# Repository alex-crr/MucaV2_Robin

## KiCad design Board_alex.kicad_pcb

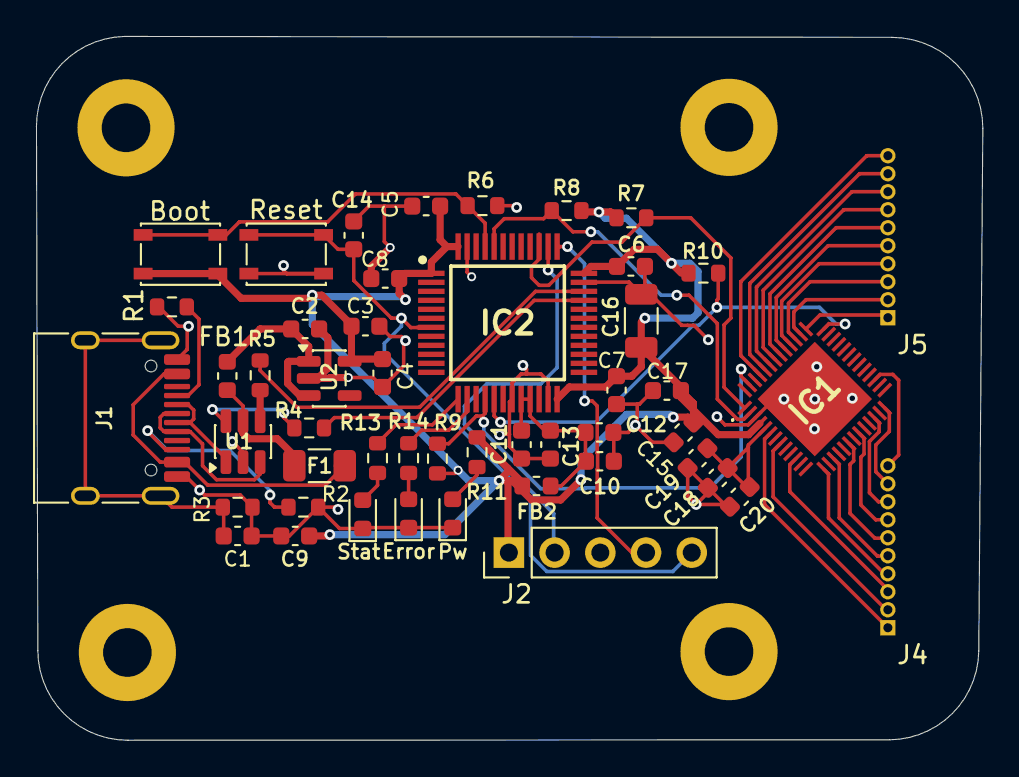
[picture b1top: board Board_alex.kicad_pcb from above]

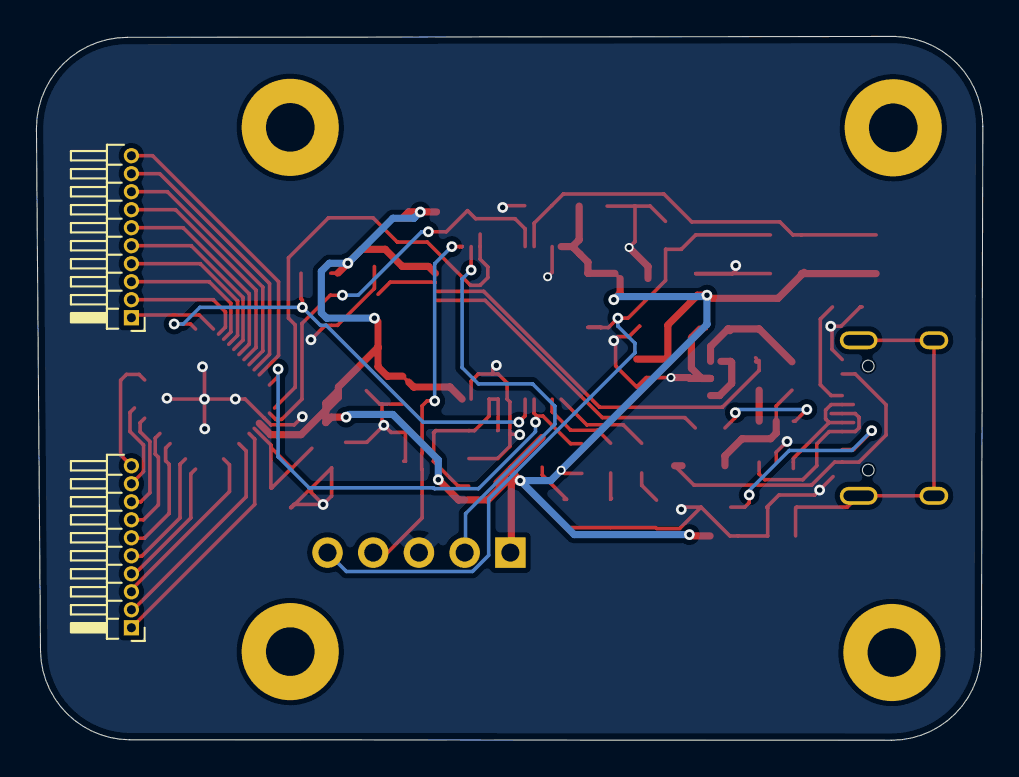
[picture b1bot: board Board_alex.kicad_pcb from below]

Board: 2 copper layers, 52.6 x 39.1 mm, 49 parts (2 on the bottom side), 49 nets.

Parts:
Boot: SW_Push; SW_SPST_PTS810
C1: C 4.7nF; C_0603_1608Metric
C2, C4: C 10uF; C_0603_1608Metric
C3, C11, C12, C20: C 1uF; C_0603_1608Metric
C5, C6, C7, C8, C10, C13, C14, C15, C19: C 100nF; C_0603_1608Metric
C9: C 4.7uF; C_0603_1608Metric
C16: C 47uF; C_1206_3216Metric
C17, C18: C 100pF; C_0603_1608Metric
Error: LED; LED_0603_1608Metric
F1: Polyfuse; Fuse_1206_3216Metric
FB1, FB2: FerriteBead; L_0603_1608Metric
IC1: IQS9150-000QFR; IQS9150000QFR
IC2: STM32G431CBT6; QFP50P900X900X160-48N
J1: USB_C_Receptacle_USB2.0_16P; USB_C_Receptacle_HRO_TYPE-C-31-M-12
J2: Conn_01x05_Pin; PinHeader_1x05_P2.54mm_Vertical
J4, J5: Conn_01x10_Pin; PinHeader_1x10_P1.00mm_Horizontal
Pw: LED; LED_0603_1608Metric
R1, R2: R 5.1k; R_0603_1608Metric
R3: R 1M; R_0603_1608Metric
R4, R5: R 22; R_0603_1608Metric
R6, R10: R 10k; R_0603_1608Metric
R7, R8, R9: R 4.7k; R_0603_1608Metric
R11, R13, R14: R 1k; R_0603_1608Metric
Reset: SW_Push; SW_SPST_PTS810
Stat: LED; LED_0603_1608Metric
U1: USBLC6-2SC6; SOT-23-6
U2: AP2112K-3.3; SOT-23-5

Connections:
+3.3V: Boot.2, C3.1, C4.1, C5.2, C6.2, C7.2, C8.2, C9.2, C15.2, C16.2, C17.2, FB2.1, IC1.4 (VDD), IC2.1 (VBAT), IC2.24 (VDD_1), IC2.36 (VDD_2), IC2.48 (VDD_3), J2.1, R7.2, R8.2, R9.1, R10.1, R11.2, U2.5 (VOUT)
+5V: C2.1, FB1.2, U2.1 (VIN), U2.3 (EN)
/Boot: Boot.1, IC2.45 (PB8-BOOT0), R6.2
/I2C_SCL: IC1.1 (SCL), IC2.39 (PA15), R7.1
/I2C_SDA: IC1.2 (SDA), IC2.44 (PB7), R8.1
/IQS_RDY: IC1.51 (RDY), IC2.16 (PB0), R9.2
/IQS_RST: IC1.39 (MCLR_/_VPP), IC2.17 (PB1), R10.2
/NRST: C14.2, IC2.7 (PG10_-_NRST), J2.5, Reset.2
/RX0: IC1.6 (RX0_/_TX0), J4.1
/RX1: IC1.8 (RX1_/_TX1), J4.2
/RX2: IC1.11 (_RX2_/_TX2), J4.3
/RX3: IC1.14 (RX3_/_TX3), J4.4
/RX4: IC1.16 (RX4_/_TX4), J4.5
/RX5: IC1.19 (RX5_/_TX5), J4.6
/RX6: IC1.21 (RX6_/_TX6), J4.7
/RX7: IC1.24 (RX7_/_TX7), J4.8
/RX8: IC1.26 (_RX8_/_TX8), J4.9
/RX9: IC1.29 (RX9_/_TX9), J4.10
/TX0: IC1.40 (TX33), J5.1
/TX1: IC1.41 (TX34), J5.2
/TX2: IC1.42 (TX35), J5.3
/TX3: IC1.43 (TX36), J5.4
/TX4: IC1.44 (TX37), J5.5
/TX5: IC1.45 (TX38), J5.6
/TX6: IC1.46 (TX39), J5.7
/TX7: IC1.47 (TX40), J5.8
/TX8: IC1.48 (TX41), J5.9
/TX9: IC1.49 (TX42), J5.10
/USB_CONN_D+: J1.A6 (D+), J1.B6 (D+), U1.3 (I/O2)
/USB_CONN_D-: J1.A7 (D-), J1.B7 (D-), U1.1 (I/O1)
/USB_D+: IC2.34 (PA12), R5.1
/USB_D-: IC2.33 (PA11), R4.2
/VBUS_PROT: F1.2, FB1.1, U1.5 (VBUS)
GND: C1.2, C2.2, C3.2, C4.2, C5.1, C6.1, C7.1, C8.1, C9.1, C10.2, C11.2, C12.2, C13.2, C14.1, C15.1, C16.1, C17.1, C18.1, C19.1, C20.1, Error.1 (K), IC1.3 (VSS), IC1.53 (GND), IC2.19 (VSSA), IC2.23 (VSS_1), IC2.35 (VSS_2), IC2.47 (VSS_3), J1.A1 (GND), J1.A12 (GND), J1.B1 (GND), J1.B12 (GND), J2.3, Pw.1 (K), R1.2, R2.2, R3.1, R6.1, Reset.1, Stat.1 (K), U1.2 (GND), U2.2 (GND)
unnamed: Error.2 (A), R14.1
unnamed: Pw.2 (A), R11.1
unnamed: R13.1, Stat.2 (A)
unnamed: F1.1, J1.A4 (VBUS), J1.A9 (VBUS), J1.B4 (VBUS), J1.B9 (VBUS)
unnamed: C18.2, C19.2, C20.2, IC1.5 (VREG)
unnamed: IC2.13 (PA5), R13.2
unnamed: IC2.14 (PA6), R14.2
unnamed: IC2.37 (PA13), J2.4
unnamed: IC2.38 (PA14), J2.2
unnamed: C10.1, C11.1, C12.1, C13.1, FB2.2, IC2.20 (VREF+), IC2.21 (VDDA)
unnamed: J1.A5 (CC1), R1.1
unnamed: J1.B5 (CC2), R2.1
unnamed: C1.1, J1.SH (SHIELD), R3.2
unnamed: R4.1, U1.6 (I/O1)
unnamed: R5.2, U1.4 (I/O2)

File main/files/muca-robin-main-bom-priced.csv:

Designators,Value,Footprint,Qty/Board,LCSC Part #,JLC Type,JLC Stock,LCSC Stock,Unit @1bd (USD),Unit @5bd (USD),Unit @10bd (USD),Unit @50bd (USD),MPN,Datasheet
C1,C 4.7nF,C_0603_1608Metric,1,,Missing,,,,,,,,
"C2,C4",C 10uF,C_0603_1608Metric,2,,Missing,,,,,,,,
"C3,C11,C12,C20",C 1uF,C_0603_1608Metric,4,,Missing,,,,,,,,
"C5,C6,C7,C8,C10,C13,C14,C15,C19",C 100nF,C_0603_1608Metric,9,,Missing,,,,,,,,
C9,C 4.7uF,C_0603_1608Metric,1,,Missing,,,,,,,,
C16,C 47uF,C_1206_3216Metric,1,,Missing,,,,,,,,
"C17,C18",C 100pF,C_0603_1608Metric,2,,Missing,,,,,,,,
"D_error1,D_power1,D_status1",LED,LED_0603_1608Metric,3,,Missing,,,,,,,,
F1,Polyfuse,Fuse_1206_3216Metric,1,,Missing,,,,,,,,
"FB1,FB2",FerriteBead,L_0603_1608Metric,2,,Missing,,,,,,,,
IC1,IQS9150-000QFR,IQS9150000QFR,1,,Missing,,,,,,,,https://www.azoteq.com/images/stories/pdf/iqs9150_datasheet.pdf
IC2,STM32G431CBT6,QFP50P900X900X160-48N,1,,Missing,,,,,,,,https://www.st.com/resource/en/datasheet/stm32g431c6.pdf
J1,USB_C_Receptacle_USB2.0_16P,USB_C_Receptacle_HRO_TYPE-C-31-M-12,1,,Missing,,,,,,,,https://www.usb.org/sites/default/files/documents/usb_type-c.zip
J2,Conn_01x05_Pin,PinHeader_1x05_P2.54mm_Vertical,1,,Missing,,,,,,,,
"J4,J5",Conn_01x10_Pin,PinHeader_1x10_P1.00mm_Horizontal,2,,Missing,,,,,,,,
"R1,R2",R 5.1k,R_0603_1608Metric,2,,Missing,,,,,,,,
R3,R 1M,R_0603_1608Metric,1,,Missing,,,,,,,,
"R4,R5",R 22,R_0603_1608Metric,2,,Missing,,,,,,,,
"R6,R10",R 10k,R_0603_1608Metric,2,,Missing,,,,,,,,
"R7,R8,R9",R 4.7k,R_0603_1608Metric,3,,Missing,,,,,,,,
"R11,R13,R14",R 1k,R_0603_1608Metric,3,,Missing,,,,,,,,
"SW1,SW2",SW_Push,SW_SPST_PTS810,2,,Missing,,,,,,,,
U1,USBLC6-2SC6,SOT-23-6,1,,Missing,,,,,,,,https://www.st.com/resource/en/datasheet/usblc6-2.pdf
U2,AP2112K-3.3,SOT-23-5,1,,Missing,,,,,,,,https://www.diodes.com/assets/Datasheets/AP2112.pdf
